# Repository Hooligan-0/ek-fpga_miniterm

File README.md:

ek-fpga_miniterm
================

VGA terminal emulator based on EK-120099 FPGA module

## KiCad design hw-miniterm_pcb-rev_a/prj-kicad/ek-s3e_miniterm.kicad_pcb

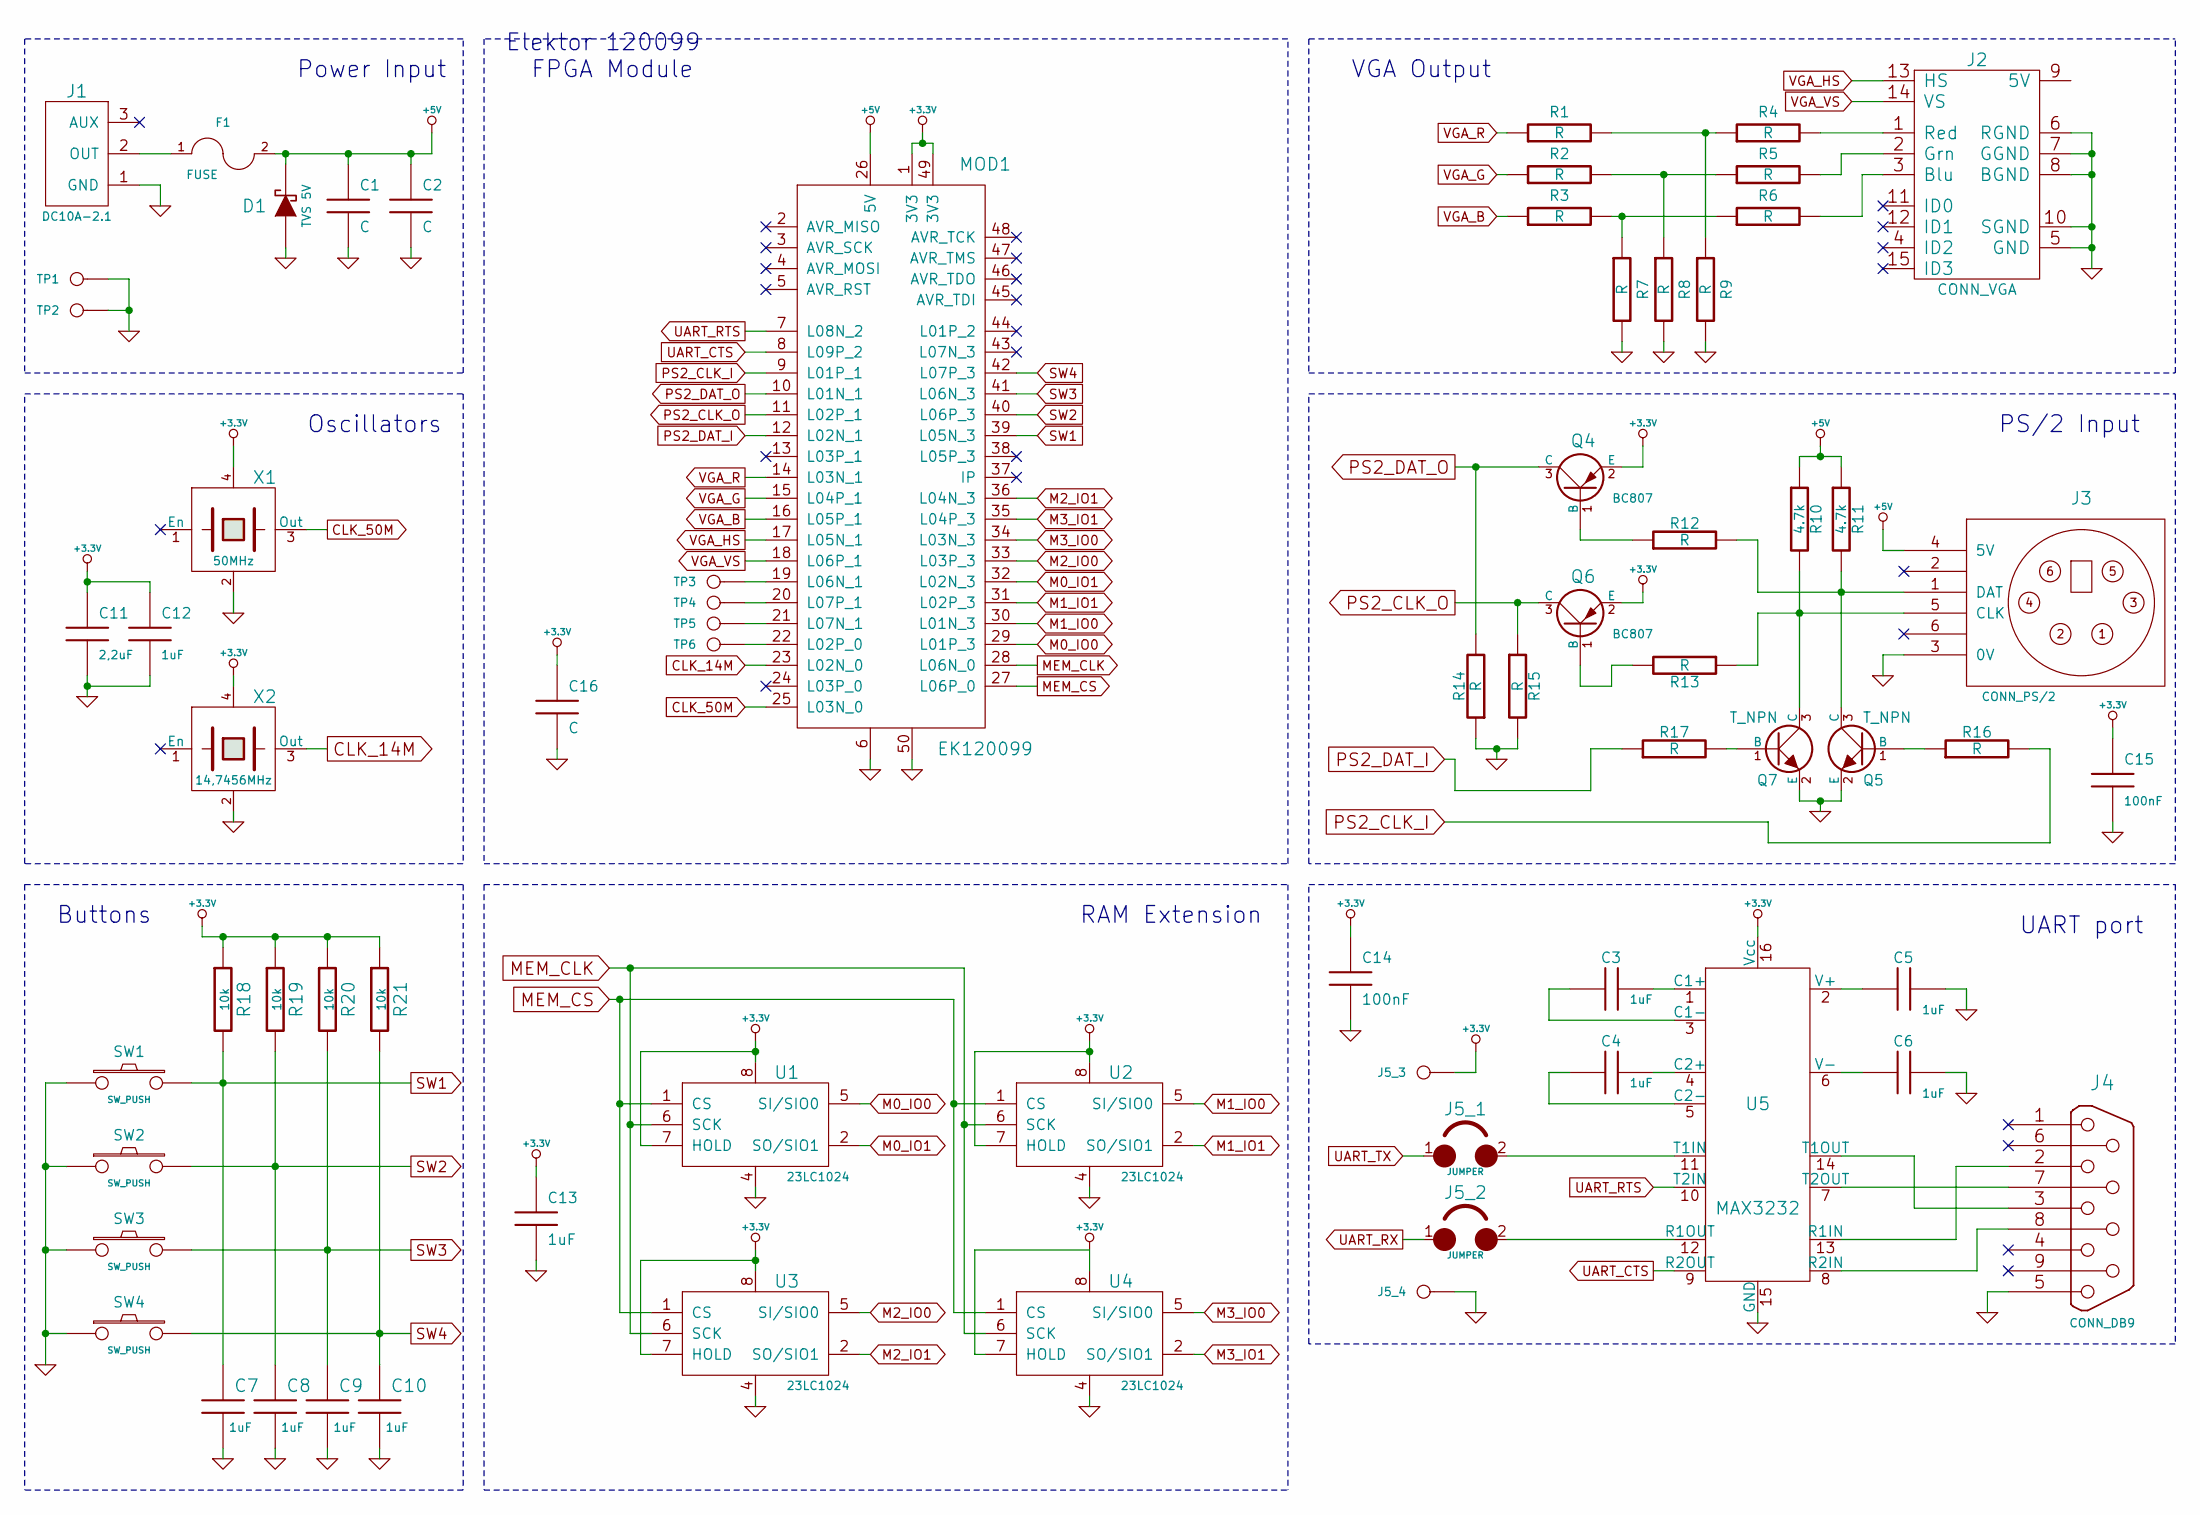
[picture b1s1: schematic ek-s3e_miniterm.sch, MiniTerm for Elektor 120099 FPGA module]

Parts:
C1, C2, C16: C
C3, C4, C5, C6, C7, C8, C9, C10, C12, C13: 1uF
C11: 2,2uF
C14, C15: 100nF
D1: TVS 5V
F1: FUSE
J1: DC10A-2.1
J2: CONN_VGA
J3: CONN_PS/2
J4: CONN_DB9
J5_1, J5_2: JUMPER
J5_3, J5_4: CONN_1
MOD1: EK120099
Q4, Q6: BC807
Q5, Q7: T_NPN
R1, R2, R3, R4, R5, R6, R7, R8, R9, R12, R13, R14, R15, R16, R17: R
R10, R11: 4.7k
R18, R19, R20, R21: 10k
SW1, SW2, SW3, SW4: SW_PUSH
TP1, TP2, TP3, TP4, TP5, TP6: CONN_1
U1, U2, U3, U4: 23LC1024
U5: MAX3232
X1: 50MHz
X2: 14,7456MHz

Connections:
+3.3V: C11.1, C12.1, C13.1, C14.1, C15.1, C16.1, J5_3.1, MOD1.1 (3V3), MOD1.49 (3V3), Q4.2 (E), Q6.2 (E), R18.1, R19.1, R20.1, R21.1, U1.7 (HOLD), U1.8, U2.7 (HOLD), U2.8, U3.7 (HOLD), U3.8, U4.7 (HOLD), U4.8, U5.16 (Vcc), X1.4, X2.4
+5V: C1.1, C2.1, D1.2 (K), F1.2, J3.4 (5V), MOD1.26 (5V), R10.1, R11.1
CLK_14M: MOD1.23 (L02N_0), X2.3 (Out)
CLK_50M: MOD1.25 (L03N_0), X1.3 (Out)
GND: C1.2, C2.2, C5.2, C6.2, C7.2, C8.2, C9.2, C10.2, C11.2, C12.2, C13.2, C14.2, C15.2, C16.2, D1.1 (A), J1.1 (GND), J2.5 (GND), J2.6 (RGND), J2.7 (GGND), J2.8 (BGND), J2.10 (SGND), J3.3 (0V), J4.5, J5_4.1, MOD1.6, MOD1.50, Q5.2 (E), Q7.2 (E), R7.2, R8.2, R9.2, R14.1, R15.2, SW1.1, SW2.1, SW3.1, SW4.1, TP1.1, TP2.1, U1.4, U2.4, U3.4, U4.4, U5.15 (GND), X1.2, X2.2
M0_IO0: MOD1.29 (L01P_3), U1.5 (SI/SIO0)
M0_IO1: MOD1.32 (L02N_3), U1.2 (SO/SIO1)
M1_IO0: MOD1.30 (L01N_3), U2.5 (SI/SIO0)
M1_IO1: MOD1.31 (L02P_3), U2.2 (SO/SIO1)
M2_IO0: MOD1.33 (L03P_3), U3.5 (SI/SIO0)
M2_IO1: MOD1.36 (L04N_3), U3.2 (SO/SIO1)
M3_IO0: MOD1.34 (L03N_3), U4.5 (SI/SIO0)
M3_IO1: MOD1.35 (L04P_3), U4.2 (SO/SIO1)
MEM_CLK: MOD1.28 (L06N_0), U1.6 (SCK), U2.6 (SCK), U3.6 (SCK), U4.6 (SCK)
MEM_CS: MOD1.27 (L06P_0), U1.1 (CS), U2.1 (CS), U3.1 (CS), U4.1 (CS)
unnamed: C6.1, U5.6 (V-)
unnamed: C4.2, U5.4 (C2+)
unnamed: C3.1, U5.3 (C1-)
unnamed: C3.2, U5.1 (C1+)
unnamed: C4.1, U5.5 (C2-)
unnamed: C5.1, U5.2 (V+)
unnamed: J4.8, U5.8 (R2IN)
unnamed: J4.2, U5.13 (R1IN)
unnamed: J5_1.2, U5.11 (T1IN)
unnamed: J5_2.2, U5.12 (R1OUT)
unnamed: J4.7, U5.7 (T2OUT)
unnamed: J4.3, U5.14 (T1OUT)
unnamed: MOD1.21 (L07N_1), TP5.1
unnamed: MOD1.19 (L06N_1), TP3.1
unnamed: MOD1.20 (L07P_1), TP4.1
unnamed: MOD1.22 (L02P_0), TP6.1
unnamed: F1.1, J1.2 (OUT)
unnamed: Q7.1 (B), R17.2
unnamed: Q5.1 (B), R16.1
unnamed: Q6.1 (B), R13.2
unnamed: Q4.1 (B), R12.1
unnamed: J2.2 (Grn), R5.2
unnamed: J2.3 (Blu), R6.2
unnamed: J2.1 (Red), R4.2
unnamed: J3.1 (DAT), Q5.3 (C), R11.2, R12.2
unnamed: J3.5 (CLK), Q7.3 (C), R10.2, R13.1
unnamed: R1.2, R4.1, R9.1
unnamed: R2.2, R5.1, R8.1
unnamed: R3.2, R6.1, R7.1
PS2_CLK_I: MOD1.9 (L01P_1), R16.2
PS2_CLK_O: MOD1.11 (L02P_1), Q6.3 (C), R15.1
PS2_DAT_I: MOD1.12 (L02N_1), R17.1
PS2_DAT_O: MOD1.10 (L01N_1), Q4.3 (C), R14.2
SW1: C7.1, MOD1.39 (L05N_3), R18.2, SW1.2
SW2: C8.1, MOD1.40 (L06P_3), R19.2, SW2.2
SW3: C9.1, MOD1.41 (L06N_3), R20.2, SW3.2
SW4: C10.1, MOD1.42 (L07P_3), R21.2, SW4.2
UART_CTS: MOD1.8 (L09P_2), U5.9 (R2OUT)
UART_RTS: MOD1.7 (L08N_2), U5.10 (T2IN)
VGA_B: MOD1.16 (L05P_1), R3.1
VGA_G: MOD1.15 (L04P_1), R2.1
VGA_HS: J2.13 (HS), MOD1.17 (L05N_1)
VGA_R: MOD1.14 (L03N_1), R1.1
VGA_VS: J2.14 (VS), MOD1.18 (L06P_1)

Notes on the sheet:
PS/2 Input
VGA Output
RAM Extension
UART port
Buttons
Oscillators
Power Input
Elektor 120099 FPGA Module

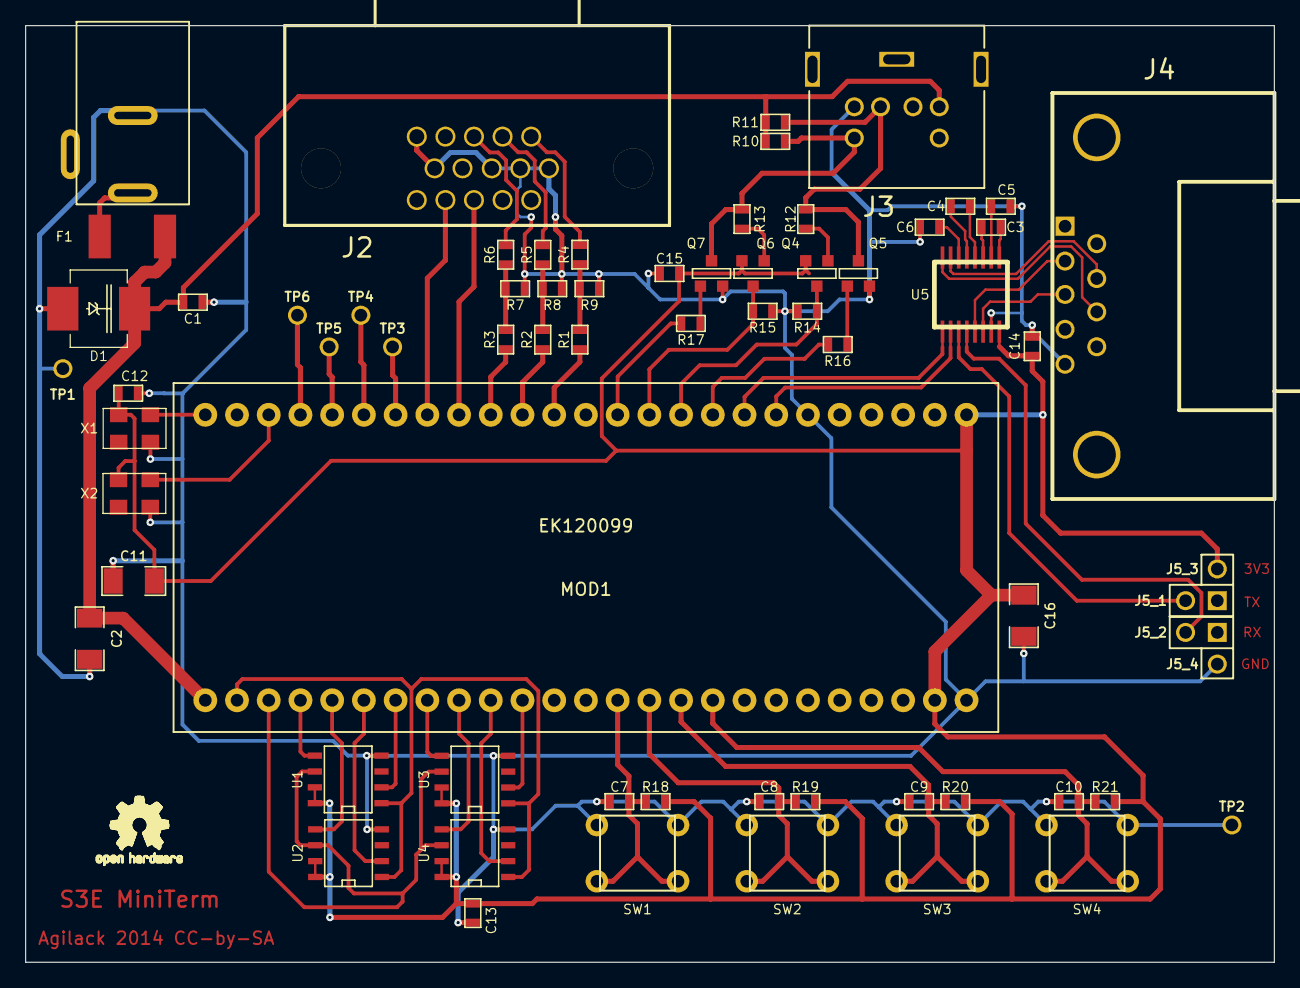
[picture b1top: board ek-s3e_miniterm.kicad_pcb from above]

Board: 2 copper layers, 100.0 x 75.0 mm, 70 parts (0 on the bottom side), 59 nets.

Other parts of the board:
ohw_logo: VAL**; ohw_logo

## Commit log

2014-04-25 --=={ Initial Import of VGA unit-test }==--
2014-05-06 = Unit-test for UART interface - This test create an echo function - Simulate RX and TX at 115200 baud - Tested on board r02 (bytes are well received)
2014-05-08 = Unit-test for external SRAM chip - Test write-to and read-from SRAM using SPI protocol - Currently limited to 1 bit spi mode (SDI and SQI not implemented) - Verified only into simulator (ISIM)
2015-05-25 = ADD: Kicad project for the first prototype
2015-05-26 = ADD: Production files for the first PCB prototype
2015-06-19 = ADD: first picture of the board (without SRAM)

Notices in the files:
hw-miniterm_pcb-rev_a/prj-kicad/ek-s3e_miniterm.kicad_pcb:
Agilack 2014 CC-by-SA
